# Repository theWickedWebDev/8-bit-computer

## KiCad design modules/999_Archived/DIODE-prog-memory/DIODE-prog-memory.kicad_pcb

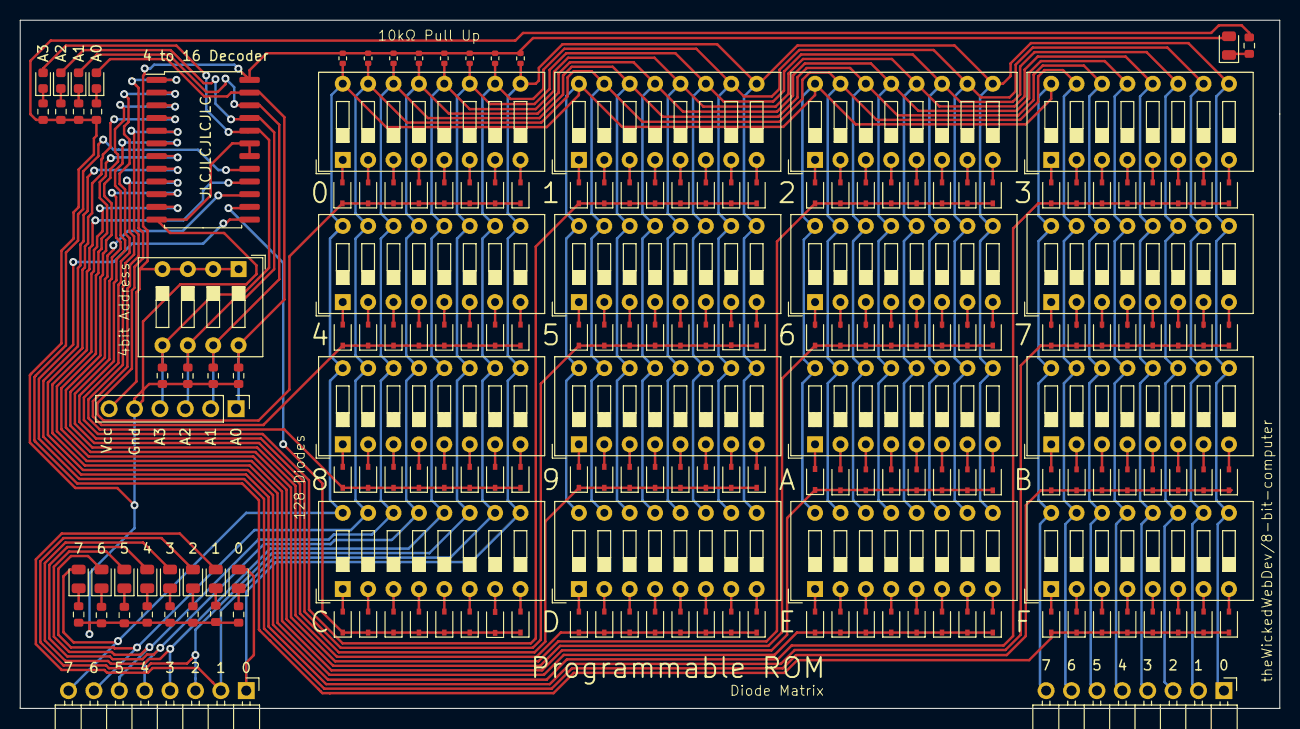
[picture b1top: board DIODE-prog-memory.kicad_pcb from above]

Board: 2 copper layers, 126.0 x 68.8 mm, 187 parts (0 on the bottom side), 171 nets.

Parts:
D1, D2, D3, D4, D5, D6, D7, D8, D9, D10, D11, D12, D13, D14, D15, D16, D17, D18, D19, D20, D21, D22, D23, D24, D25, D26, D27, D28, D29, D30, D31, D32, D33, D34, D35, D36, D37, D38, D39, D40, D41, D42, D43, D44, D45, D46, D47, D48, D49, D50, D51, D52, D53, D54, D55, D56, D57, D58, D59, D60, D61, D62, D63, D64, D65, D66, D67, D68, D69, D70, D71, D72, D73, D74, D75, D76, D77, D78, D79, D80, D81, D82, D83, D84, D85, D86, D87, D88, D89, D90, D91, D92, D93, D94, D95, D96, D97, D98, D99, D100, D101, D102, D103, D104, D105, D106, D107, D108, D109, D110, D111, D112, D113, D114, D115, D116, D117, D118, D119, D120, D121, D122, D123, D124, D125, D126, D127, D128: 1N4148W; D_SOD-323
J1, J2: Conn_01x8; PinHeader_1x08_P2.54mm_Horizontal
J3: Conn_01x6; PinHeader_1x06_P2.54mm_Vertical
R1, R2, R3, R4, R5, R6, R7, R8: 0603WAF1002T5E; R_0402_1005Metric
SW1: SW_DIP_x04; SW_DIP_SPSTx04_Slide_9.78x12.34mm_W7.62mm_P2.54mm
SW2, SW3, SW4, SW5, SW6, SW7, SW8, SW9, SW10, SW11, SW12, SW13, SW14, SW15, SW16, SW17: SW_DIP_x08; SW_DIP_SPSTx08_Slide_9.78x22.5mm_W7.62mm_P2.54mm
U1: 74HC154D,653; SOIC-24W_7.5x15.4mm_P1.27mm
U2, U3, U4, U5, U7, U9, U11, U13, U15, U17, U19, U21, U22, U23, U24, U25, U31: 0603WAF1001T5E; R_0603_1608Metric
U6, U8, U10, U12, U14, U16, U18, U20, U30: NCD0805R1; LED_0805_2012Metric
U26, U27, U28, U29: 19-213_Y2C-CQ2R2L_3T(CY); LED_0603_1608Metric

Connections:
A: J1.8, J2.8, R1.2, SW2.16, SW3.16, SW4.16, SW5.16, SW6.16, SW7.16, SW8.16, SW9.16, SW10.16, SW11.16, SW12.16, SW13.16, SW14.16, SW15.16, SW16.16, SW17.16, U20.2
B: J1.7, J2.7, R2.2, SW2.15, SW3.15, SW4.15, SW5.15, SW6.15, SW7.15, SW8.15, SW9.15, SW10.15, SW11.15, SW12.15, SW13.15, SW14.15, SW15.15, SW16.15, SW17.15, U18.2
C: J1.6, J2.6, R3.2, SW2.14, SW3.14, SW4.14, SW5.14, SW6.14, SW7.14, SW8.14, SW9.14, SW10.14, SW11.14, SW12.14, SW13.14, SW14.14, SW15.14, SW16.14, SW17.14, U16.2
D: J1.5, J2.5, R4.2, SW2.13, SW3.13, SW4.13, SW5.13, SW6.13, SW7.13, SW8.13, SW9.13, SW10.13, SW11.13, SW12.13, SW13.13, SW14.13, SW15.13, SW16.13, SW17.13, U14.2
E: J1.4, J2.4, R5.2, SW2.12, SW3.12, SW4.12, SW5.12, SW6.12, SW7.12, SW8.12, SW9.12, SW10.12, SW11.12, SW12.12, SW13.12, SW14.12, SW15.12, SW16.12, SW17.12, U12.2
F: J1.3, J2.3, R6.2, SW2.11, SW3.11, SW4.11, SW5.11, SW6.11, SW7.11, SW8.11, SW9.11, SW10.11, SW11.11, SW12.11, SW13.11, SW14.11, SW15.11, SW16.11, SW17.11, U10.2
G: J1.2, J2.2, R7.2, SW2.10, SW3.10, SW4.10, SW5.10, SW6.10, SW7.10, SW8.10, SW9.10, SW10.10, SW11.10, SW12.10, SW13.10, SW14.10, SW15.10, SW16.10, SW17.10, U8.2
GND: J3.5, U1.12, U1.18, U1.19, U2.2, U3.2, U4.2, U5.2, U7.2, U9.2, U11.2, U13.2, U15.2, U17.2, U19.2, U21.2, U22.2, U23.2, U24.2, U25.2, U31.1
H: J1.1, J2.1, R8.2, SW2.9, SW3.9, SW4.9, SW5.9, SW6.9, SW7.9, SW8.9, SW9.9, SW10.9, SW11.9, SW12.9, SW13.9, SW14.9, SW15.9, SW16.9, SW17.9, U6.2
unnamed: D1.1, D18.1, D19.1, D20.1, D21.1, D22.1, D23.1, D24.1, U1.6
unnamed: D1.2, SW4.8
unnamed: D2.1, D3.1, D4.1, D5.1, D6.1, D7.1, D8.1, D9.1, U1.1
unnamed: D2.2, SW2.8
unnamed: D3.2, SW2.7
unnamed: D4.2, SW2.6
unnamed: D5.2, SW2.5
unnamed: D6.2, SW2.4
unnamed: D7.2, SW2.3
unnamed: D8.2, SW2.2
unnamed: D9.2, SW2.1
unnamed: D10.1, D11.1, D12.1, D13.1, D14.1, D15.1, D16.1, D17.1, U1.2
unnamed: D10.2, SW3.8
unnamed: D11.2, SW3.7
unnamed: D12.2, SW3.6
unnamed: D13.2, SW3.5
unnamed: D14.2, SW3.4
unnamed: D15.2, SW3.3
unnamed: D16.2, SW3.2
unnamed: D17.2, SW3.1
unnamed: D18.2, SW4.7
unnamed: D19.2, SW4.6
unnamed: D20.2, SW4.5
unnamed: D21.2, SW4.4
unnamed: D22.2, SW4.3
unnamed: D23.2, SW4.2
unnamed: D24.2, SW4.1
unnamed: D25.1, D26.1, D27.1, D28.1, D29.1, D30.1, D31.1, D32.1, U1.5
unnamed: D25.2, SW5.8
unnamed: D26.2, SW5.7
unnamed: D27.2, SW5.6
unnamed: D28.2, SW5.5
unnamed: D29.2, SW5.4
unnamed: D30.2, SW5.3
unnamed: D31.2, SW5.2
unnamed: D32.2, SW5.1
unnamed: D33.1, D34.1, D35.1, D36.1, D37.1, D38.1, D39.1, D40.1, U1.10
unnamed: D33.2, SW6.8
unnamed: D34.2, SW6.7
unnamed: D35.2, SW6.6
unnamed: D36.2, SW6.5
unnamed: D37.2, SW6.4
unnamed: D38.2, SW6.3
unnamed: D39.2, SW6.2
unnamed: D40.2, SW6.1
unnamed: D41.1, D42.1, D43.1, D44.1, D45.1, D46.1, D47.1, D48.1, U1.9
unnamed: D41.2, SW7.8
unnamed: D42.2, SW7.7
unnamed: D43.2, SW7.6
unnamed: D44.2, SW7.5
unnamed: D45.2, SW7.4
unnamed: D46.2, SW7.3
unnamed: D47.2, SW7.2
unnamed: D48.2, SW7.1
unnamed: D49.1, D50.1, D51.1, D52.1, D53.1, D54.1, D55.1, D56.1, U1.15
unnamed: D49.2, SW8.8
unnamed: D50.2, SW8.7
unnamed: D51.2, SW8.6
unnamed: D52.2, SW8.5
unnamed: D53.2, SW8.4
unnamed: D54.2, SW8.3
unnamed: D55.2, SW8.2
unnamed: D56.2, SW8.1
unnamed: D57.1, D58.1, D59.1, D60.1, D61.1, D62.1, D63.1, D64.1, U1.14
unnamed: D57.2, SW9.8
unnamed: D58.2, SW9.7
unnamed: D59.2, SW9.6
unnamed: D60.2, SW9.5
unnamed: D61.2, SW9.4
unnamed: D62.2, SW9.3
unnamed: D63.2, SW9.2
unnamed: D64.2, SW9.1
unnamed: D65.1, D66.1, D67.1, D68.1, D69.1, D70.1, D71.1, D72.1, U1.4
unnamed: D65.2, SW10.8
unnamed: D66.2, SW10.7
unnamed: D67.2, SW10.6
unnamed: D68.2, SW10.5
unnamed: D69.2, SW10.4
unnamed: D70.2, SW10.3
unnamed: D71.2, SW10.2
unnamed: D72.2, SW10.1
unnamed: D73.1, D74.1, D75.1, D76.1, D77.1, D78.1, D79.1, D80.1, U1.3
unnamed: D73.2, SW11.8
unnamed: D74.2, SW11.7
unnamed: D75.2, SW11.6
unnamed: D76.2, SW11.5
unnamed: D77.2, SW11.4
unnamed: D78.2, SW11.3
unnamed: D79.2, SW11.2
unnamed: D80.2, SW11.1
unnamed: D81.1, D82.1, D83.1, D84.1, D85.1, D86.1, D87.1, D88.1, U1.8
unnamed: D81.2, SW12.8
unnamed: D82.2, SW12.7
unnamed: D83.2, SW12.6
unnamed: D84.2, SW12.5
unnamed: D85.2, SW12.4
unnamed: D86.2, SW12.3
unnamed: D87.2, SW12.2
unnamed: D88.2, SW12.1
unnamed: D89.1, D90.1, D91.1, D92.1, D93.1, D94.1, D95.1, D96.1, U1.7
unnamed: D89.2, SW13.8
unnamed: D90.2, SW13.7
unnamed: D91.2, SW13.6
unnamed: D92.2, SW13.5
unnamed: D93.2, SW13.4
unnamed: D94.2, SW13.3
unnamed: D95.2, SW13.2
unnamed: D96.2, SW13.1
unnamed: D97.2, SW14.8
unnamed: D98.2, SW15.8
unnamed: D99.2, SW14.7
unnamed: D98.1, D100.1, D102.1, D104.1, D106.1, D108.1, D110.1, D112.1, U1.17
unnamed: D100.2, SW15.7
unnamed: D97.1, D99.1, D101.1, D103.1, D105.1, D107.1, D109.1, D111.1, U1.13
unnamed: D101.2, SW14.6
unnamed: D102.2, SW15.6
unnamed: D103.2, SW14.5
unnamed: D104.2, SW15.5
unnamed: D105.2, SW14.4
unnamed: D106.2, SW15.4
unnamed: D107.2, SW14.3
unnamed: D108.2, SW15.3
unnamed: D109.2, SW14.2
unnamed: D110.2, SW15.2
unnamed: D111.2, SW14.1
unnamed: D112.2, SW15.1
unnamed: D113.1, D115.1, D117.1, D119.1, D121.1, D123.1, D125.1, D127.1, U1.11
unnamed: D113.2, SW16.8
unnamed: D114.1, D116.1, D118.1, D120.1, D122.1, D124.1, D126.1, D128.1, U1.16
unnamed: D114.2, SW17.8
unnamed: D115.2, SW16.7
unnamed: D116.2, SW17.7
unnamed: D117.2, SW16.6
unnamed: D118.2, SW17.6
unnamed: D119.2, SW16.5
unnamed: D120.2, SW17.5
unnamed: D121.2, SW16.4
unnamed: D122.2, SW17.4
unnamed: D123.2, SW16.3
unnamed: D124.2, SW17.3
unnamed: D125.2, SW16.2
unnamed: D126.2, SW17.2
unnamed: D127.2, SW16.1
unnamed: D128.2, SW17.1
unnamed: J3.1, SW1.8, U1.23, U5.1, U29.2
unnamed: J3.2, SW1.7, U1.22, U4.1, U28.2
unnamed: J3.3, SW1.6, U1.21, U3.1, U27.2
unnamed: J3.4, SW1.5, U1.20, U2.1, U26.2
unnamed: U6.1, U7.1
unnamed: U8.1, U9.1
unnamed: U10.1, U11.1
unnamed: U12.1, U13.1
unnamed: U14.1, U15.1
unnamed: U16.1, U17.1
unnamed: U18.1, U19.1
unnamed: U20.1, U21.1
unnamed: U22.1, U26.1
unnamed: U23.1, U27.1
unnamed: U24.1, U28.1
unnamed: U25.1, U29.1
unnamed: U30.1, U31.2
VCC: J3.6, R1.1, R2.1, R3.1, R4.1, R5.1, R6.1, R7.1, R8.1, SW1.1, SW1.2, SW1.3, SW1.4, U1.24, U30.2

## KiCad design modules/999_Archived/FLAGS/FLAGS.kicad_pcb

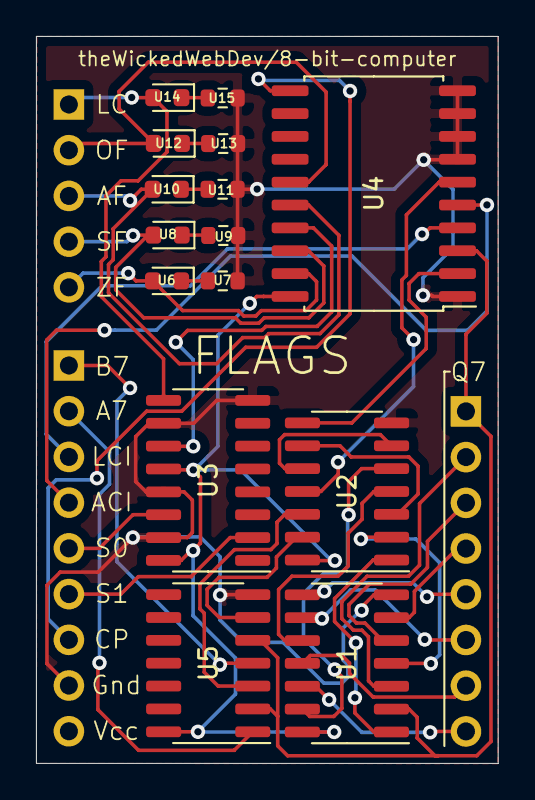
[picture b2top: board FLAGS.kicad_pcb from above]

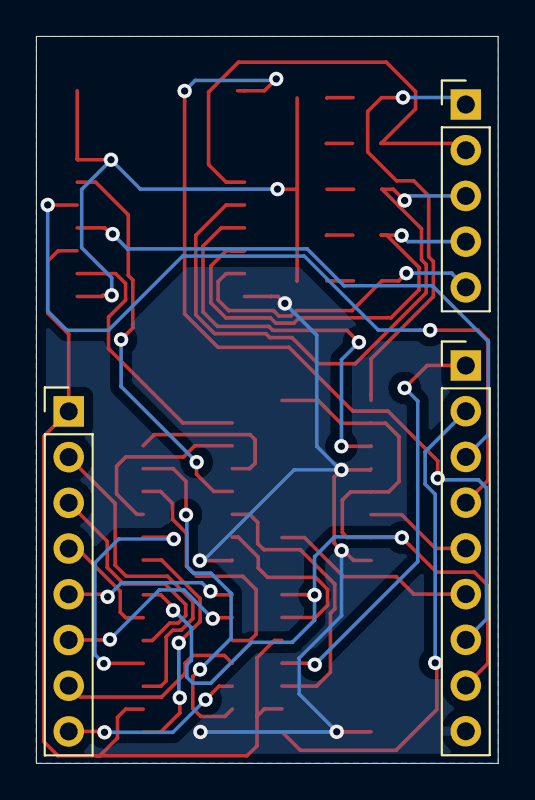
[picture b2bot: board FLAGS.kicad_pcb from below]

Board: 2 copper layers, 25.7 x 40.4 mm, 18 parts (3 on the bottom side), 38 nets.

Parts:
J1: Conn_01x05; PinHeader_1x05_P2.54mm_Vertical
J2: Conn_01x08; PinHeader_1x08_P2.54mm_Vertical
J3: Conn_01x09; PinHeader_1x09_P2.54mm_Vertical
U1: MC74AC02DR2G; SOIC-14_3.9x8.7mm_P1.27mm
U2: 74HC08D,653; SOIC-14_3.9x8.7mm_P1.27mm
U3: 74HC153D,653; SOIC-16_3.9x9.9mm_P1.27mm
U4: 74HCT574; SOIC-20W_7.5x12.8mm_P1.27mm
U5: 74HC86; SOIC-14_3.9x8.7mm_P1.27mm
U6, U8, U10, U12, U14: 19-213_Y2C-CQ2R2L_3T(CY); LED_0603_1608Metric
U7, U9, U11, U13, U15: 0603WAF1001T5E; R_0603_1608Metric

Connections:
/LOGICAL_CARRY_OUT: U3.11, U4.17
/OVERFLOW: U2.11, U4.6
/ZERO_SUM: U2.8, U4.2
A7: J3.2, U5.1
ARITH_CARRY_IN: J3.4, U4.5
ARITMETIC_CARRY_FLAG: J1.3, U4.16, U10.2
B7: J3.1, U5.4
CARRY_IN_SEL_0: J3.5, U3.14
CARRY_IN_SEL_1: J3.6, U3.2
CLOCK: J3.7, U4.11
GND: J3.8, U1.7, U2.7, U3.8, U3.10, U3.13, U3.15, U4.1, U4.7, U4.8, U4.9, U4.10, U5.7, U7.2, U9.2, U11.2, U13.2, U15.2
LOGICAL_CARRY_FLAG: J1.1, U3.9, U14.2
LOGICAL_CARRY_IN: J3.3, U4.4
unnamed: U1.1, U2.1
unnamed: U1.4, U2.2
unnamed: U1.10, U2.4
unnamed: U1.13, U2.5
unnamed: U2.3, U2.9
unnamed: U2.6, U2.10
unnamed: U2.12, U5.3
unnamed: U2.13, U5.6
unnamed: U6.1, U7.1
unnamed: U8.1, U9.1
unnamed: U10.1, U11.1
unnamed: U12.1, U13.1
unnamed: U14.1, U15.1
OVERFLOW_FLAG: J1.2, U4.15, U12.2
Q0: J2.8, U1.12
Q1: J2.7, U1.11
Q2: J2.6, U1.9
Q3: J2.5, U1.8
Q4: J2.4, U1.6
Q5: J2.3, U1.5
Q6: J2.2, U1.3
Q7: J2.1, U1.2, U4.3, U5.2, U5.5
SIGN_FLAG: J1.4, U4.18, U8.2
VCC: J3.9, U1.14, U2.14, U3.12, U3.16, U4.20, U5.14
ZERO_FLAG: J1.5, U4.19, U6.2

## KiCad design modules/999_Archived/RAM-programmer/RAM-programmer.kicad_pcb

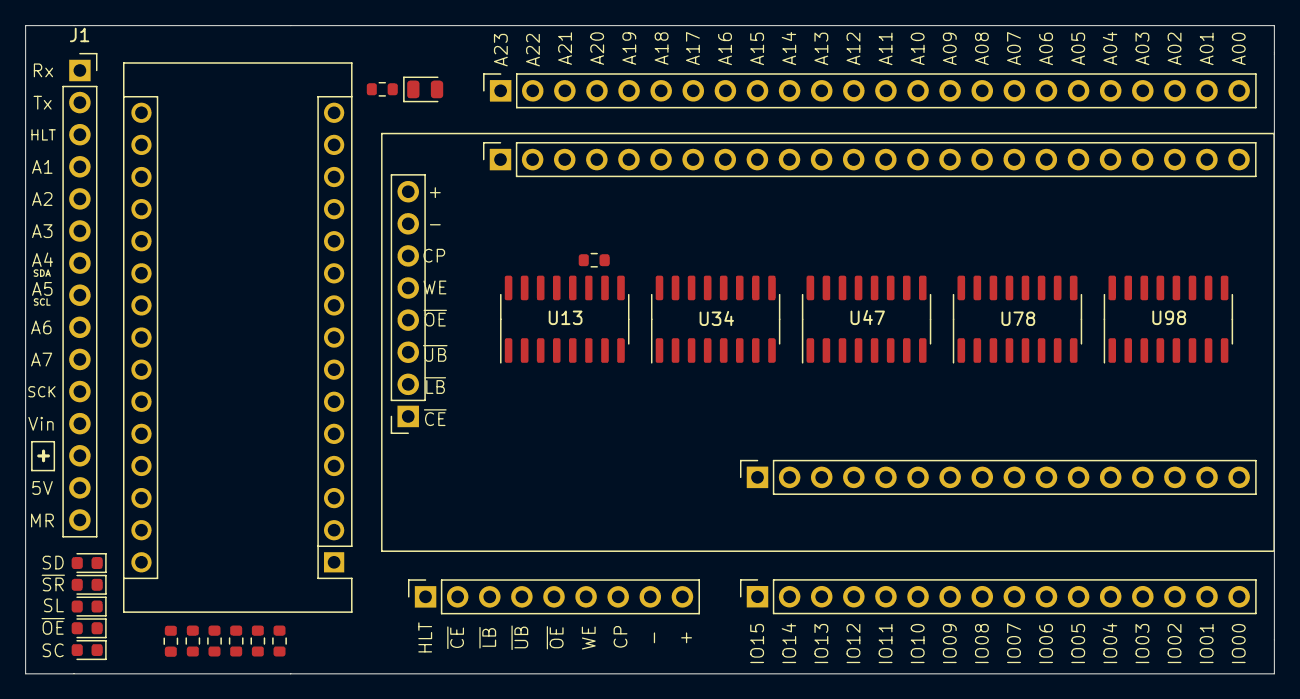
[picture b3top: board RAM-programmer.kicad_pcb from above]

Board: 2 copper layers, 98.8 x 51.3 mm, 27 parts (0 on the bottom side), 77 nets, no tracks yet.

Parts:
A1: Arduino_Nano_Every; Arduino_Nano
J1: Conn_01x15; PinSocket_1x15_P2.54mm_Vertical
J2, J5: Conn_01x16; PinSocket_1x16_P2.54mm_Vertical
J3, J6: Conn_01x24; PinSocket_1x24_P2.54mm_Vertical
J4: Conn_01x08; PinSocket_1x08_P2.54mm_Vertical
J7: Conn_01x09; PinSocket_1x09_P2.54mm_Vertical
U1: NCD0805R1; LED_0805_2012Metric
U2, U4, U6, U8, U10, U12, U14, U81: 0603WAF1001T5E; R_0603_1608Metric
U3, U5, U7, U9: 19-217_BHC-ZL1M2RY_3T; LED_0603_1608Metric
U11: 19-213_Y2C-CQ2R2L_3T(CY); LED_0603_1608Metric
U13, U34, U47, U78, U98: 74AHC595; SOIC-16_3.9x9.9mm_P1.27mm

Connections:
CLOCK: J4.6, J7.7, U5.2
GND: A1.4, A1.29, J4.7, J7.8, U2.2, U4.2, U6.2, U8.2, U10.2, U12.2, U13.8, U34.8, U47.8, U78.8, U98.8
HALT: A1.19, J1.3, J7.1
unnamed: A1.1, J1.2
unnamed: A1.2, J1.1
unnamed: A1.16, J1.11
unnamed: A1.20, J1.4
unnamed: A1.21, J1.5
unnamed: A1.22, J1.6
unnamed: A1.23, J1.7
unnamed: A1.24, J1.8
unnamed: A1.25, J1.9
unnamed: A1.26, J1.10
unnamed: A1.27, J1.14
unnamed: A1.30, J1.12
unnamed: J1.15, U14.1
unnamed: J2.1, J5.1, U13.15
unnamed: J2.2, J5.2, U13.1
unnamed: J2.3, J5.3, U13.2
unnamed: J2.4, J5.4, U13.3
unnamed: J2.5, J5.5, U13.4
unnamed: J2.6, J5.6, U13.5
unnamed: J2.7, J5.7, U13.6
unnamed: J2.8, J5.8, U13.7
unnamed: J2.9, J5.9, U34.15
unnamed: J2.10, J5.10, U34.1
unnamed: J2.11, J5.11, U34.2
unnamed: J2.12, J5.12, U34.3
unnamed: J2.13, J5.13, U34.4
unnamed: J2.14, J5.14, U34.5
unnamed: J2.15, J5.15, U34.6
unnamed: J2.16, J5.16, U34.7
unnamed: J3.1, J6.1, U47.15
unnamed: J3.2, J6.2, U47.1
unnamed: J3.3, J6.3, U47.2
unnamed: J3.4, J6.4, U47.3
unnamed: J3.5, J6.5, U47.4
unnamed: J3.6, J6.6, U47.5
unnamed: J3.7, J6.7, U47.6
unnamed: J3.8, J6.8, U47.7
unnamed: J3.9, J6.9, U78.15
unnamed: J3.10, J6.10, U78.1
unnamed: J3.11, J6.11, U78.2
unnamed: J3.12, J6.12, U78.3
unnamed: J3.13, J6.13, U78.4
unnamed: J3.14, J6.14, U78.5
unnamed: J3.15, J6.15, U78.6
unnamed: J3.16, J6.16, U78.7
unnamed: J3.17, J6.17, U98.15
unnamed: J3.18, J6.18, U98.1
unnamed: J3.19, J6.19, U98.2
unnamed: J3.20, J6.20, U98.3
unnamed: J3.21, J6.21, U98.4
unnamed: J3.22, J6.22, U98.5
unnamed: J3.23, J6.23, U98.6
unnamed: J3.24, J6.24, U98.7
unnamed: U1.1, U2.1
unnamed: U3.1, U4.1
unnamed: U5.1, U6.1
unnamed: U7.1, U8.1
unnamed: U9.1, U10.1
unnamed: U11.1, U12.1
unnamed: U13.9, U34.14
unnamed: U34.9, U47.14
unnamed: U47.9, U78.14
unnamed: U78.9, U98.14
SR_CLOCK: A1.15, U13.11, U34.11, U47.11, U78.11, U98.11
SR_DATA: A1.6, U3.2
SR_LATCH: A1.8, U7.2, U13.12, U34.12, U47.12, U78.12, U98.12
VCC: A1.3, J1.13, J4.8, J7.9, U1.2, U13.16, U14.2, U34.16, U47.16, U78.16, U81.1, U98.16
WE: A1.14, J4.5, J7.6
~CE: A1.10, J4.1, J7.2
~LB: A1.11, J4.2, J7.3
~OE: A1.13, J4.4, J7.5
~SR_OE: A1.9, U9.2, U13.13, U34.13, U47.13, U78.13, U81.2, U98.13
~SR_RESET: A1.7, U11.2, U13.10, U34.10, U47.10, U78.10, U98.10
~UB: A1.12, J4.3, J7.4

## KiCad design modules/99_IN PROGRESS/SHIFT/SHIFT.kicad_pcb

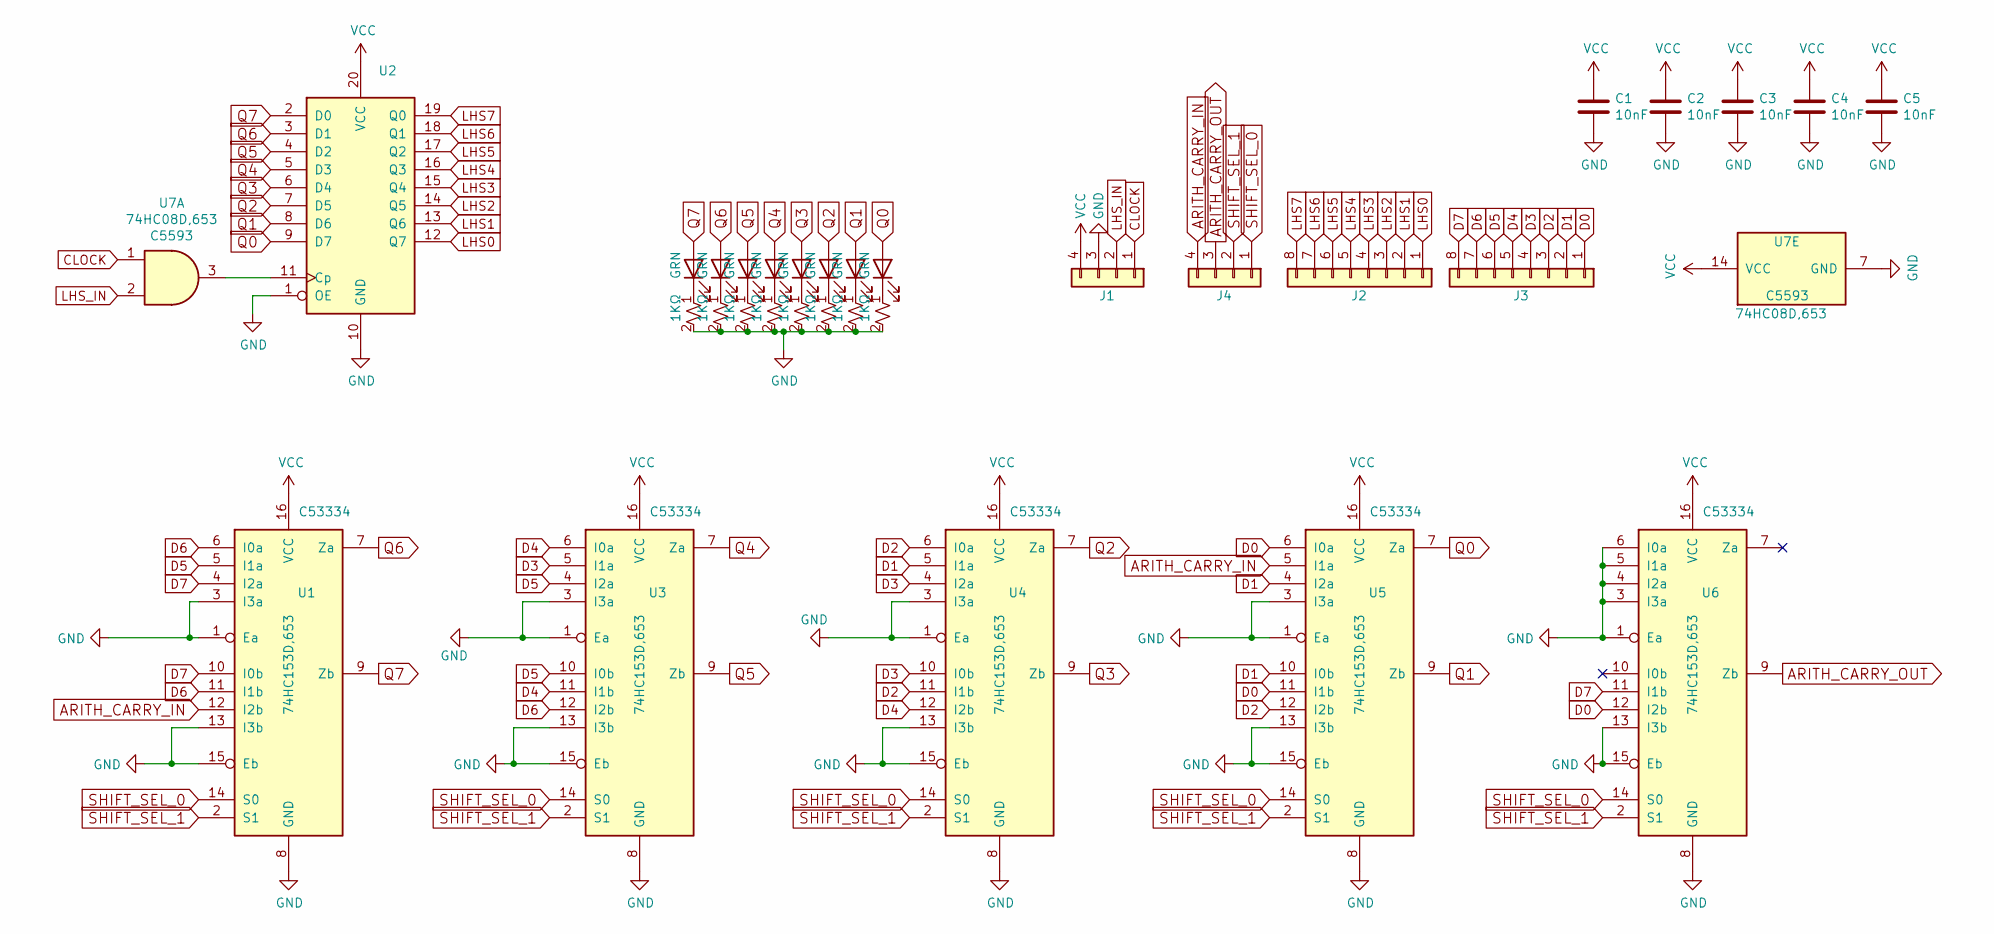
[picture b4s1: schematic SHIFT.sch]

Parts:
C1, C2, C3, C4, C5: 0603B103K500NT; C_0603_1608Metric
D1, D2, D3, D4, D5, D6, D7, D8: C2297; LED_0805_2012Metric
J1, J4: Conn_01x04; PinHeader_1x04_P2.54mm_Vertical
J2, J3: Conn_01x08; PinHeader_1x08_P2.54mm_Vertical
U1, U3, U4, U5, U6: 74HC153D,653; SOIC-16_3.9x9.9mm_P1.27mm
U2: 74HCT574; SOIC-20W_7.5x12.8mm_P1.27mm
U7: 74HC08D,653; SOIC-14_3.9x8.7mm_P1.27mm
U8, U9, U10, U11, U12, U13, U14, U15: 0603WAF1001T5E; R_0603_1608Metric

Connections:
ARITH_CARRY_IN: J4.4, U1.12 (I2b), U5.5 (I1a)
ARITH_CARRY_OUT: J4.3, U6.9 (Zb)
CLOCK: J1.1, U7.1
D0: J3.1, U5.6 (I0a), U5.11 (I1b), U6.12 (I2b)
D1: J3.2, U4.5 (I1a), U5.4 (I2a), U5.10 (I0b)
D2: J3.3, U4.6 (I0a), U4.11 (I1b), U5.12 (I2b)
D3: J3.4, U3.5 (I1a), U4.4 (I2a), U4.10 (I0b)
D4: J3.5, U3.6 (I0a), U3.11 (I1b), U4.12 (I2b)
D5: J3.6, U1.5 (I1a), U3.4 (I2a), U3.10 (I0b)
D6: J3.7, U1.6 (I0a), U1.11 (I1b), U3.12 (I2b)
D7: J3.8, U1.4 (I2a), U1.10 (I0b), U6.11 (I1b)
GND: C1.2, C2.2, C3.2, C4.2, C5.2, J1.3, U1.1 (Ea), U1.3 (I3a), U1.8 (GND), U1.13 (I3b), U1.15 (Eb), U2.1 (OE), U2.10 (GND), U3.1 (Ea), U3.3 (I3a), U3.8 (GND), U3.13 (I3b), U3.15 (Eb), U4.1 (Ea), U4.3 (I3a), U4.8 (GND), U4.13 (I3b), U4.15 (Eb), U5.1 (Ea), U5.3 (I3a), U5.8 (GND), U5.13 (I3b), U5.15 (Eb), U6.1 (Ea), U6.3 (I3a), U6.4 (I2a), U6.5 (I1a), U6.6 (I0a), U6.8 (GND), U6.13 (I3b), U6.15 (Eb), U7.7 (GND), U8.2, U9.2, U10.2, U11.2, U12.2, U13.2, U14.2, U15.2
LHS0: J2.1, U2.12 (Q7)
LHS1: J2.2, U2.13 (Q6)
LHS2: J2.3, U2.14 (Q5)
LHS3: J2.4, U2.15 (Q4)
LHS4: J2.5, U2.16 (Q3)
LHS5: J2.6, U2.17 (Q2)
LHS6: J2.7, U2.18 (Q1)
LHS7: J2.8, U2.19 (Q0)
LHS_IN: J1.2, U7.2
unnamed: D1.1 (K), U8.1
unnamed: D2.1 (K), U9.1
unnamed: D3.1 (K), U10.1
unnamed: D4.1 (K), U11.1
unnamed: D5.1 (K), U12.1
unnamed: D6.1 (K), U13.1
unnamed: D7.1 (K), U14.1
unnamed: D8.1 (K), U15.1
unnamed: U2.11 (Cp), U7.3
Q0: D8.2 (A), U2.9 (D7), U5.7 (Za)
Q1: D7.2 (A), U2.8 (D6), U5.9 (Zb)
Q2: D6.2 (A), U2.7 (D5), U4.7 (Za)
Q3: D5.2 (A), U2.6 (D4), U4.9 (Zb)
Q4: D4.2 (A), U2.5 (D3), U3.7 (Za)
Q5: D3.2 (A), U2.4 (D2), U3.9 (Zb)
Q6: D2.2 (A), U1.7 (Za), U2.3 (D1)
Q7: D1.2 (A), U1.9 (Zb), U2.2 (D0)
SHIFT_SEL_0: J4.1, U1.14 (S0), U3.14 (S0), U4.14 (S0), U5.14 (S0), U6.14 (S0)
SHIFT_SEL_1: J4.2, U1.2 (S1), U3.2 (S1), U4.2 (S1), U5.2 (S1), U6.2 (S1)
VCC: C1.1, C2.1, C3.1, C4.1, C5.1, J1.4, U1.16 (VCC), U2.20 (VCC), U3.16 (VCC), U4.16 (VCC), U5.16 (VCC), U6.16 (VCC), U7.14 (VCC)

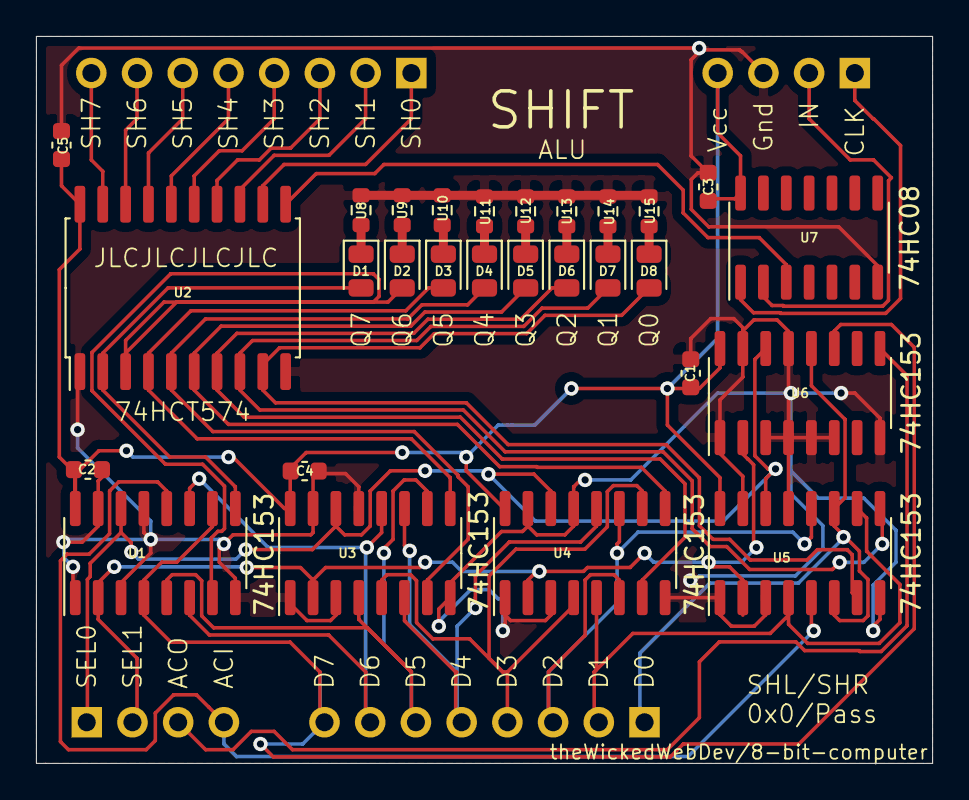
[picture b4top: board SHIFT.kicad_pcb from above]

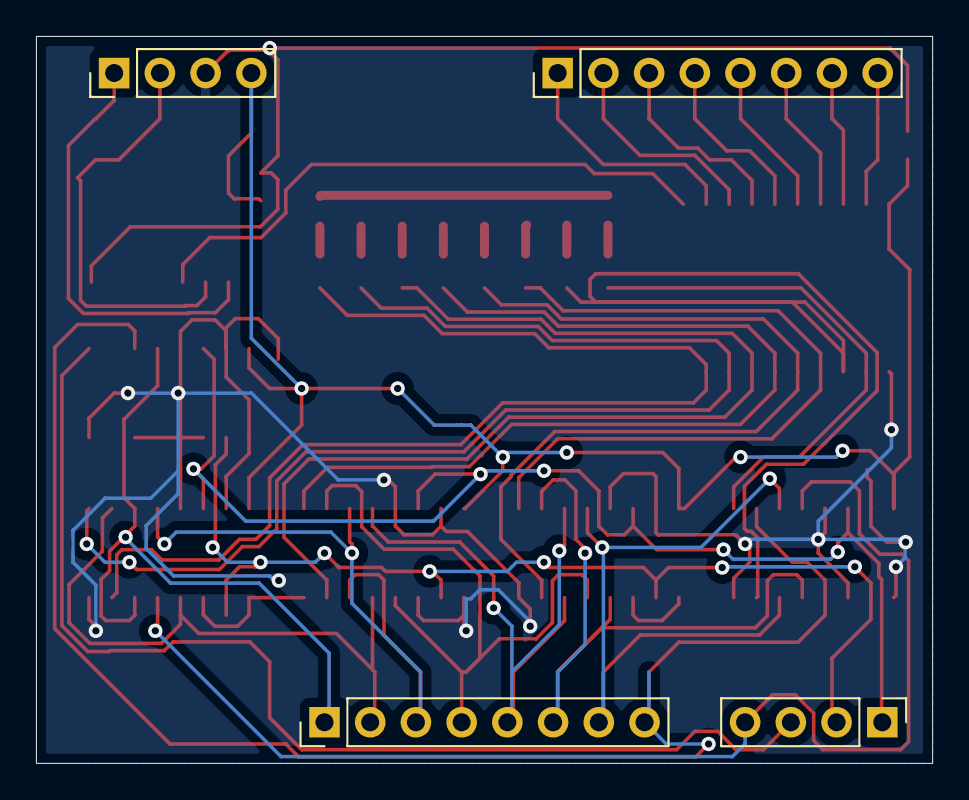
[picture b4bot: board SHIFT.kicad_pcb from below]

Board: 2 copper layers, 49.8 x 40.4 mm, 32 parts (4 on the bottom side), 41 nets.

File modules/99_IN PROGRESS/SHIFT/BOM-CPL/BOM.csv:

"Source:","/Users/stephenyoung/KiCad/8-bit-computer/modules/SHIFT/SHIFT.sch"
"Date:","Wednesday, September 22, 2021 at 08:52:35 PM"
"Tool:","Eeschema (5.1.10-1-10_14)"
"Generator:","/Users/stephenyoung/KiCad/8-bit-computer/bom_csv_grouped_by_value.py"
"Component Count:","32"

"Individual Components:"

"Item","Qty","Reference(s)","Value","LibPart","Footprint","Datasheet","C","Color","Desc","Description","JCLC","R"
"","","C1","0603B103K500NT","JLCPCB:0603B103K500NT","Capacitor_SMD:C_0603_1608Metric","https://datasheet.lcsc.com/lcsc/2102081402_FH-Guangdong-Feng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","10nF","","","X7R ±10% 50V 10nF 0603 Multilayer Ceramic Capacitors MLCC - SMD/SMT ROHS","C57112",""
"","","C2","0603B103K500NT","JLCPCB:0603B103K500NT","Capacitor_SMD:C_0603_1608Metric","https://datasheet.lcsc.com/lcsc/2102081402_FH-Guangdong-Feng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","10nF","","","X7R ±10% 50V 10nF 0603 Multilayer Ceramic Capacitors MLCC - SMD/SMT ROHS","C57112",""
"","","C3","0603B103K500NT","JLCPCB:0603B103K500NT","Capacitor_SMD:C_0603_1608Metric","https://datasheet.lcsc.com/lcsc/2102081402_FH-Guangdong-Feng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","10nF","","","X7R ±10% 50V 10nF 0603 Multilayer Ceramic Capacitors MLCC - SMD/SMT ROHS","C57112",""
"","","C4","0603B103K500NT","JLCPCB:0603B103K500NT","Capacitor_SMD:C_0603_1608Metric","https://datasheet.lcsc.com/lcsc/2102081402_FH-Guangdong-Feng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","10nF","","","X7R ±10% 50V 10nF 0603 Multilayer Ceramic Capacitors MLCC - SMD/SMT ROHS","C57112",""
"","","C5","0603B103K500NT","JLCPCB:0603B103K500NT","Capacitor_SMD:C_0603_1608Metric","https://datasheet.lcsc.com/lcsc/2102081402_FH-Guangdong-Feng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","10nF","","","X7R ±10% 50V 10nF 0603 Multilayer Ceramic Capacitors MLCC - SMD/SMT ROHS","C57112",""
"","","D1","C2297","JLCPCB:C2297","LED_SMD:LED_0805_2012Metric","~","","GRN","520~530nm Green 0805 Light Emitting Diodes (LED) ROHS","","C2297",""
"","","D2","C2297","JLCPCB:C2297","LED_SMD:LED_0805_2012Metric","~","","GRN","520~530nm Green 0805 Light Emitting Diodes (LED) ROHS","","C2297",""
"","","D3","C2297","JLCPCB:C2297","LED_SMD:LED_0805_2012Metric","~","","GRN","520~530nm Green 0805 Light Emitting Diodes (LED) ROHS","","C2297",""
"","","D4","C2297","JLCPCB:C2297","LED_SMD:LED_0805_2012Metric","~","","GRN","520~530nm Green 0805 Light Emitting Diodes (LED) ROHS","","C2297",""
"","","D5","C2297","JLCPCB:C2297","LED_SMD:LED_0805_2012Metric","~","","GRN","520~530nm Green 0805 Light Emitting Diodes (LED) ROHS","","C2297",""
"","","D6","C2297","JLCPCB:C2297","LED_SMD:LED_0805_2012Metric","~","","GRN","520~530nm Green 0805 Light Emitting Diodes (LED) ROHS","","C2297",""
"","","D7","C2297","JLCPCB:C2297","LED_SMD:LED_0805_2012Metric","~","","GRN","520~530nm Green 0805 Light Emitting Diodes (LED) ROHS","","C2297",""
"","","D8","C2297","JLCPCB:C2297","LED_SMD:LED_0805_2012Metric","~","","GRN","520~530nm Green 0805 Light Emitting Diodes (LED) ROHS","","C2297",""
"","","J1","Conn_01x04","Connector_Generic:Conn_01x04","Connector_PinHeader_2.54mm:PinHeader_1x04_P2.54mm_Vertical","~","","","","","",""
"","","J2","Conn_01x08","Connector_Generic:Conn_01x08","Connector_PinHeader_2.54mm:PinHeader_1x08_P2.54mm_Vertical","~","","","","","",""
"","","J3","Conn_01x08","Connector_Generic:Conn_01x08","Connector_PinHeader_2.54mm:PinHeader_1x08_P2.54mm_Vertical","~","","","","","",""
"","","J4","Conn_01x04","Connector_Generic:Conn_01x04","Connector_PinHeader_2.54mm:PinHeader_1x04_P2.54mm_Vertical","~","","","","","",""
"","","U1","74HC153D,653","JLCPCB:74HC153D,653","Package_SO:SOIC-16_3.9x9.9mm_P1.27mm","http://www.ti.com/lit/gpn/sn74LS153","","","","","C53334",""
"","","U2","74HCT574","JLCPCB:74HCT574","Package_SO:SOIC-20W_7.5x12.8mm_P1.27mm","http://www.ti.com/lit/gpn/sn74HCT574","","","","","C88576",""
"","","U3","74HC153D,653","JLCPCB:74HC153D,653","Package_SO:SOIC-16_3.9x9.9mm_P1.27mm","http://www.ti.com/lit/gpn/sn74LS153","","","","","C53334",""
"","","U4","74HC153D,653","JLCPCB:74HC153D,653","Package_SO:SOIC-16_3.9x9.9mm_P1.27mm","http://www.ti.com/lit/gpn/sn74LS153","","","","","C53334",""
"","","U5","74HC153D,653","JLCPCB:74HC153D,653","Package_SO:SOIC-16_3.9x9.9mm_P1.27mm","http://www.ti.com/lit/gpn/sn74LS153","","","","","C53334",""
"","","U6","74HC153D,653","JLCPCB:74HC153D,653","Package_SO:SOIC-16_3.9x9.9mm_P1.27mm","http://www.ti.com/lit/gpn/sn74LS153","","","","","C53334",""
"","","U7","74HC08D,653","JLCPCB:74HC08D,653","Package_SO:SOIC-14_3.9x8.7mm_P1.27mm","https://datasheet.lcsc.com/lcsc/2006241032_Nexperia-74HC08D,653_C5593.pdf","","","","","C5593",""
"","","U8","0603WAF1001T5E","JLCPCB:0603WAF1001T5E","Resistor_SMD:R_0603_1608Metric","","","","","","C21190","1KΩ"
"","","U9","0603WAF1001T5E","JLCPCB:0603WAF1001T5E","Resistor_SMD:R_0603_1608Metric","","","","","","C21190","1KΩ"
"","","U10","0603WAF1001T5E","JLCPCB:0603WAF1001T5E","Resistor_SMD:R_0603_1608Metric","","","","","","C21190","1KΩ"
"","","U11","0603WAF1001T5E","JLCPCB:0603WAF1001T5E","Resistor_SMD:R_0603_1608Metric","","","","","","C21190","1KΩ"
"","","U12","0603WAF1001T5E","JLCPCB:0603WAF1001T5E","Resistor_SMD:R_0603_1608Metric","","","","","","C21190","1KΩ"
"","","U13","0603WAF1001T5E","JLCPCB:0603WAF1001T5E","Resistor_SMD:R_0603_1608Metric","","","","","","C21190","1KΩ"
"","","U14","0603WAF1001T5E","JLCPCB:0603WAF1001T5E","Resistor_SMD:R_0603_1608Metric","","","","","","C21190","1KΩ"
"","","U15","0603WAF1001T5E","JLCPCB:0603WAF1001T5E","Resistor_SMD:R_0603_1608Metric","","","","","","C21190","1KΩ"



"Collated Components:"

"Item","Qty","Reference(s)","Value","LibPart","Footprint","Datasheet","C","Color","Desc","Description","JCLC","R"
"1","5","C1, C2, C3, C4, C5","0603B103K500NT","JLCPCB:0603B103K500NT","Capacitor_SMD:C_0603_1608Metric","https://datasheet.lcsc.com/lcsc/2102081402_FH-Guangdong-Feng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","10nF","","","X7R ±10% 50V 10nF 0603 Multilayer Ceramic Capacitors MLCC - SMD/SMT ROHS","C57112",""
"2","8","D1, D2, D3, D4, D5, D6, D7, D8","C2297","JLCPCB:C2297","LED_SMD:LED_0805_2012Metric","~","","GRN","520~530nm Green 0805 Light Emitting Diodes (LED) ROHS","","C2297",""
"3","2","J1, J4","Conn_01x04","Connector_Generic:Conn_01x04","Connector_PinHeader_2.54mm:PinHeader_1x04_P2.54mm_Vertical","~","","","","","",""
"4","2","J2, J3","Conn_01x08","Connector_Generic:Conn_01x08","Connector_PinHeader_2.54mm:PinHeader_1x08_P2.54mm_Vertical","~","","","","","",""
"5","5","U1, U3, U4, U5, U6","74HC153D,653","JLCPCB:74HC153D,653","Package_SO:SOIC-16_3.9x9.9mm_P1.27mm","http://www.ti.com/lit/gpn/sn74LS153","","","","","C53334",""
"6","1","U2","74HCT574","JLCPCB:74HCT574","Package_SO:SOIC-20W_7.5x12.8mm_P1.27mm","http://www.ti.com/lit/gpn/sn74HCT574","","","","","C88576",""
"7","1","U7","74HC08D,653","JLCPCB:74HC08D,653","Package_SO:SOIC-14_3.9x8.7mm_P1.27mm","https://datasheet.lcsc.com/lcsc/2006241032_Nexperia-74HC08D,653_C5593.pdf","","","","","C5593",""
"8","8","U8, U9, U10, U11, U12, U13, U14, U15","0603WAF1001T5E","JLCPCB:0603WAF1001T5E","Resistor_SMD:R_0603_1608Metric","","","","","","C21190","1KΩ"
